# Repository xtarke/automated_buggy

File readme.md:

# Buggy AWD

Baseado em [Projeto PI3](https://github.com/luscasos/PI3-carro) de __Lucas Odair Silva.__

## Informações gerais

Projeto da placa eletrônica de potência para o acionamento de um Buggy 4x4. Um conector de 26-vias faz a conexão das seguintes placas:

- [Arduino Uno](./arduino/shield/)
- [MSP-EXP430G2](./msp430/shield_exp430g2)
- [MSP-EXP430FR2355](./msp430/shield_exp430fr2355)
- [Raspberry Pi](./rasp/)

## Características

- Controle independente dos motores (lado esquerdo e lado direito)
- Sensores de velocidade [Encoder](https://www.filipeflop.com/produto/sensor-de-velocidade-encoder/)
- Monitoramento de bateria de LiPo
- Sensor de linha dual
- Sensor ultrassom
- Comunicação Bluetooth (UART)

# Hardware

## Acionamento dos motores

Circuito final de alimentação dos motores, com queda de 0,4V de tensão na carga em relação a VCC e corrente de polarização externa de 640pA, não exigindo muita corrente do microcontrolador.

## Comunicação

## Aferição de velocidade

## Baterias
Para alimentar o carro foram escolhidas duas baterias de LIPO, de 3,7V e 1200mAh, conectadas em série, o que resulta em 7,4V de tensão.

## Regulador de tensão
Como o conjunto de baterias tem como tensão 7,4V na saída, é necessário baixar a tensão para níveis aceitáveis para o microcontrolador e modulo bluetooth, no caso foi usado um regulador ajustável Step-up-down, por questão de disponibilidade, mesmo esse sendo superdimensionado para a aplicação em questão, já que suporta correntes de até 5A e nesse caso não passa de 200mA.

## Medição da tensão das baterias
Como regra geral, não se pode descarregar uma bateria abaixo de uma certa tensão, com as usadas nesse projeto não é diferente, não sendo recomendado baixar a tensão da marca dos 3V, como o sistema possui duas baterias é necessário medir a tensão delas individualmente. O conversor analógico digital do microcontrolador tem como tensão base 3V, então é preciso baixar as tensões para menos de 3V, o circuito usado para isso é o diferencial com ampop, que pode dar um ganho menor que 1, sem usar tensão negativa. O Ampop escolhido foi o LM324, com ganho de 1/3 para a tensão superior (bateria 1 em serie com a bateria 2), e de 2/3 para a tensão media (bateria 1).

## Placa de circuito

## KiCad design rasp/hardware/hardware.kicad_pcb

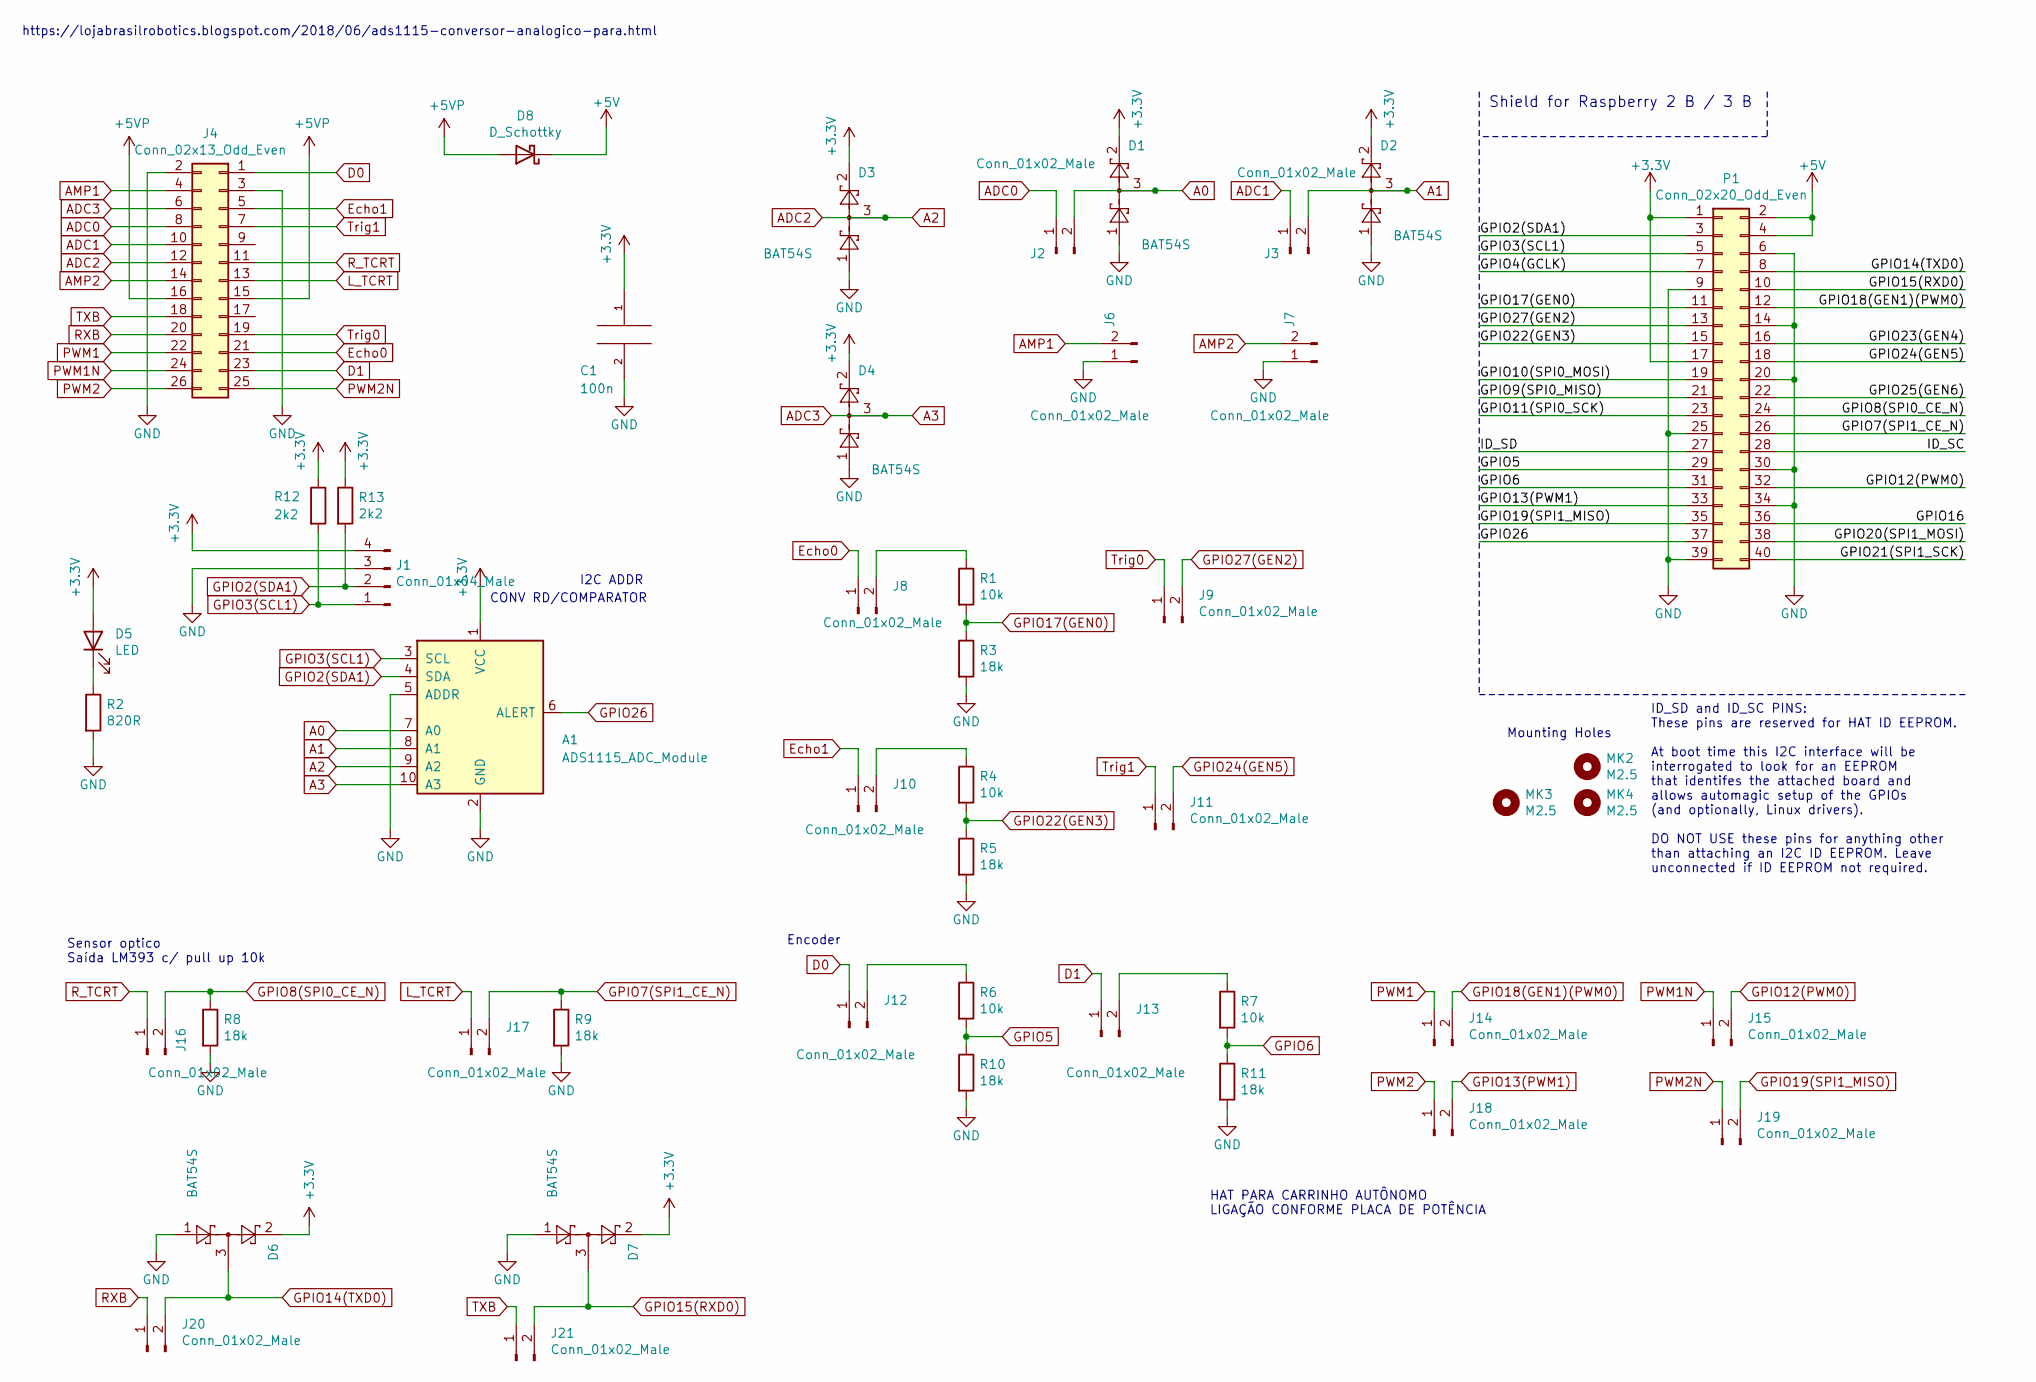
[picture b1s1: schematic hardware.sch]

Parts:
A1: ADS1115_ADC_Module; ADC1115_ADC_Module
C1: 100n; C_0805_2012Metric_Pad1.15x1.40mm_HandSolder
D1, D2, D3, D4, D6, D7: BAT54S; SOT-23
D5: LED; LED_0805_2012Metric
D8: D_Schottky; D_SMB
J1: Conn_01x04_Male; PinHeader_1x04_P2.54mm_Horizontal
J2, J3, J6, J7, J8, J9, J10, J11, J12, J13, J14, J15, J16, J17, J18, J19, J20, J21: Conn_01x02_Male; PinHeader_1x02_P2.54mm_Vertical
J4: Conn_02x13_Odd_Even; IDC-Header_2x13_P2.54mm_Vertical
MK2, MK3, MK4: M2.5; MountingHole_2.7mm_M2.5
P1: Conn_02x20_Odd_Even; PinSocket_2x20_P2.54mm_Vertical
R1, R4, R6, R7: 10k; R_0805_2012Metric
R2: 820R; R_0805_2012Metric
R3, R5, R8, R9, R10, R11: 18k; R_0805_2012Metric
R12, R13: 2k2; R_0805_2012Metric

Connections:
+3V3: A1.1 (VCC), C1.1, D1.2, D2.2, D3.2, D4.2, D5.2 (A), D6.2, D7.2, J1.4, P1.1, P1.17, R12.1, R13.1
+5V: D8.1 (K), P1.2, P1.4
+5VP: D8.2 (A), J4.15, J4.16
/GPIO4(GCLK): P1.7
/GPIO9(SPI0_MISO): P1.21
/GPIO10(SPI0_MOSI): P1.19
/GPIO11(SPI0_SCK): P1.23
/GPIO16: P1.36
/GPIO20(SPI1_MOSI): P1.38
/GPIO21(SPI1_SCK): P1.40
/GPIO23(GEN4): P1.16
/GPIO25(GEN6): P1.22
/ID_SC: P1.28
/ID_SD: P1.27
A0: A1.7 (A0), D1.3, J2.2
A1: A1.8 (A1), D2.3, J3.2
A2: A1.9 (A2), D3.3, J4.12
A3: A1.10 (A3), D4.3, J4.6
ADC0: J2.1, J4.8
ADC1: J3.1, J4.10
AMP1: J4.4, J6.2
AMP2: J4.14, J7.2
D0: J4.1, J12.1
D1: J4.23, J13.1
Echo0: J4.21, J8.1
Echo1: J4.5, J10.1
GND: A1.2 (GND), A1.5 (ADDR), C1.2, D1.1, D2.1, D3.1, D4.1, D6.1, D7.1, J1.3, J4.2, J4.3, J6.1, J7.1, P1.6, P1.9, P1.14, P1.20, P1.25, P1.30, P1.34, P1.39, R2.2, R3.2, R5.2, R8.2, R9.2, R10.2, R11.2
GPIO2(SDA1): A1.4 (SDA), J1.2, P1.3, R13.2
GPIO3(SCL1): A1.3 (SCL), J1.1, P1.5, R12.2
GPIO5: P1.29, R6.2, R10.1
GPIO6: P1.31, R7.2, R11.1
GPIO7(SPI1_CE_N): J17.2, P1.26, R9.1
GPIO8(SPI0_CE_N): J16.2, P1.24, R8.1
GPIO12(PWM0): J15.2, P1.32
GPIO13(PWM1): J18.2, P1.33
GPIO14(TXD0): D6.3, J20.2, P1.8
GPIO15(RXD0): D7.3, J21.2, P1.10
GPIO17(GEN0): P1.11, R1.2, R3.1
GPIO18(GEN1)(PWM0): J14.2, P1.12
GPIO19(SPI1_MISO): J19.2, P1.35
GPIO22(GEN3): P1.15, R4.2, R5.1
GPIO24(GEN5): J11.2, P1.18
GPIO26: A1.6 (ALERT), P1.37
GPIO27(GEN2): J9.2, P1.13
L_TCRT: J4.13, J17.1
unnamed: D5.1 (K), R2.1
unnamed: J8.2, R1.1
unnamed: J10.2, R4.1
unnamed: J12.2, R6.1
unnamed: J13.2, R7.1
PWM1: J4.22, J14.1
PWM1N: J4.24, J15.1
PWM2: J4.26, J18.1
PWM2N: J4.25, J19.1
RXB: J4.20, J20.1
R_TCRT: J4.11, J16.1
TXB: J4.18, J21.1
Trig0: J4.19, J9.1
Trig1: J4.7, J11.1

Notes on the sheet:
ID_SD and ID_SC PINS: These pins are reserved for HAT ID EEPROM. At boot time this I2C interface will be interrogated to look for an EEPROM that identifes the attached board and allows automagic setup of the GPIOs (and optionally, Linux drivers). DO NOT USE these pins for anything other than attach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
Mounting Holes
Shield for Raspberry 2 B / 3 B
Encoder
Sensor optico Saída LM393 c/ pull up 10k
HAT PARA CARRINHO AUTÔNOMO LIGAÇÃO CONFORME PLACA DE POTÊNCIA
https://lojabrasilrobotics.blogspot.com/2018/06/ads1115-conversor-analogico-para.html
I2C ADDR
CONV RD/COMPARATOR

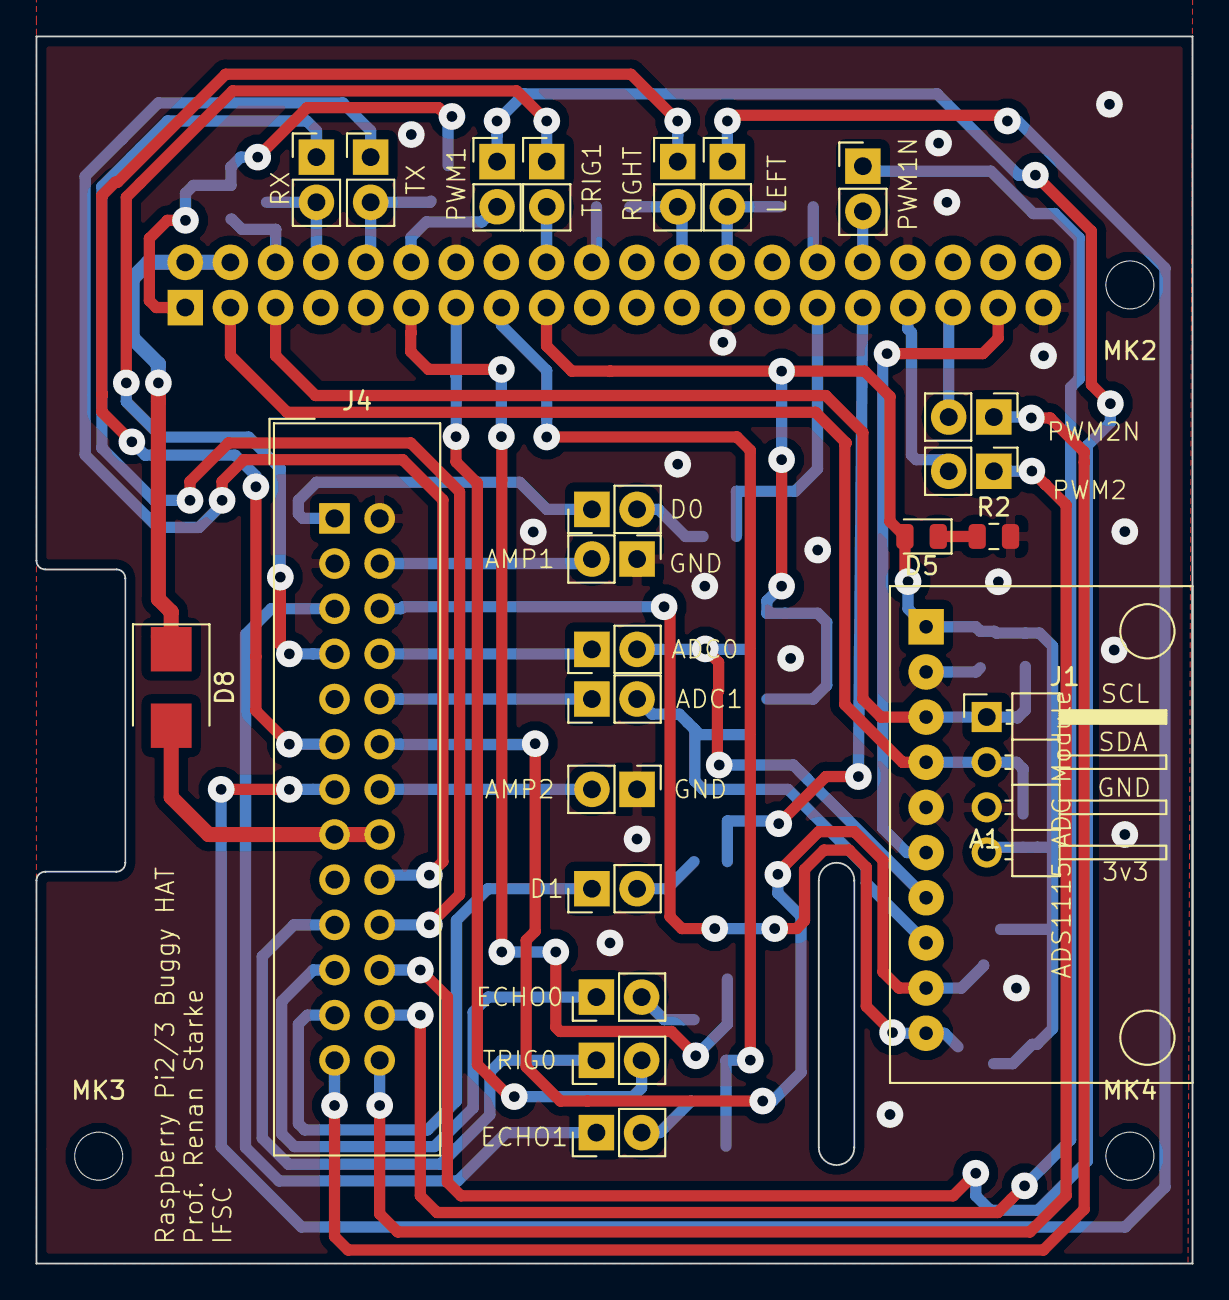
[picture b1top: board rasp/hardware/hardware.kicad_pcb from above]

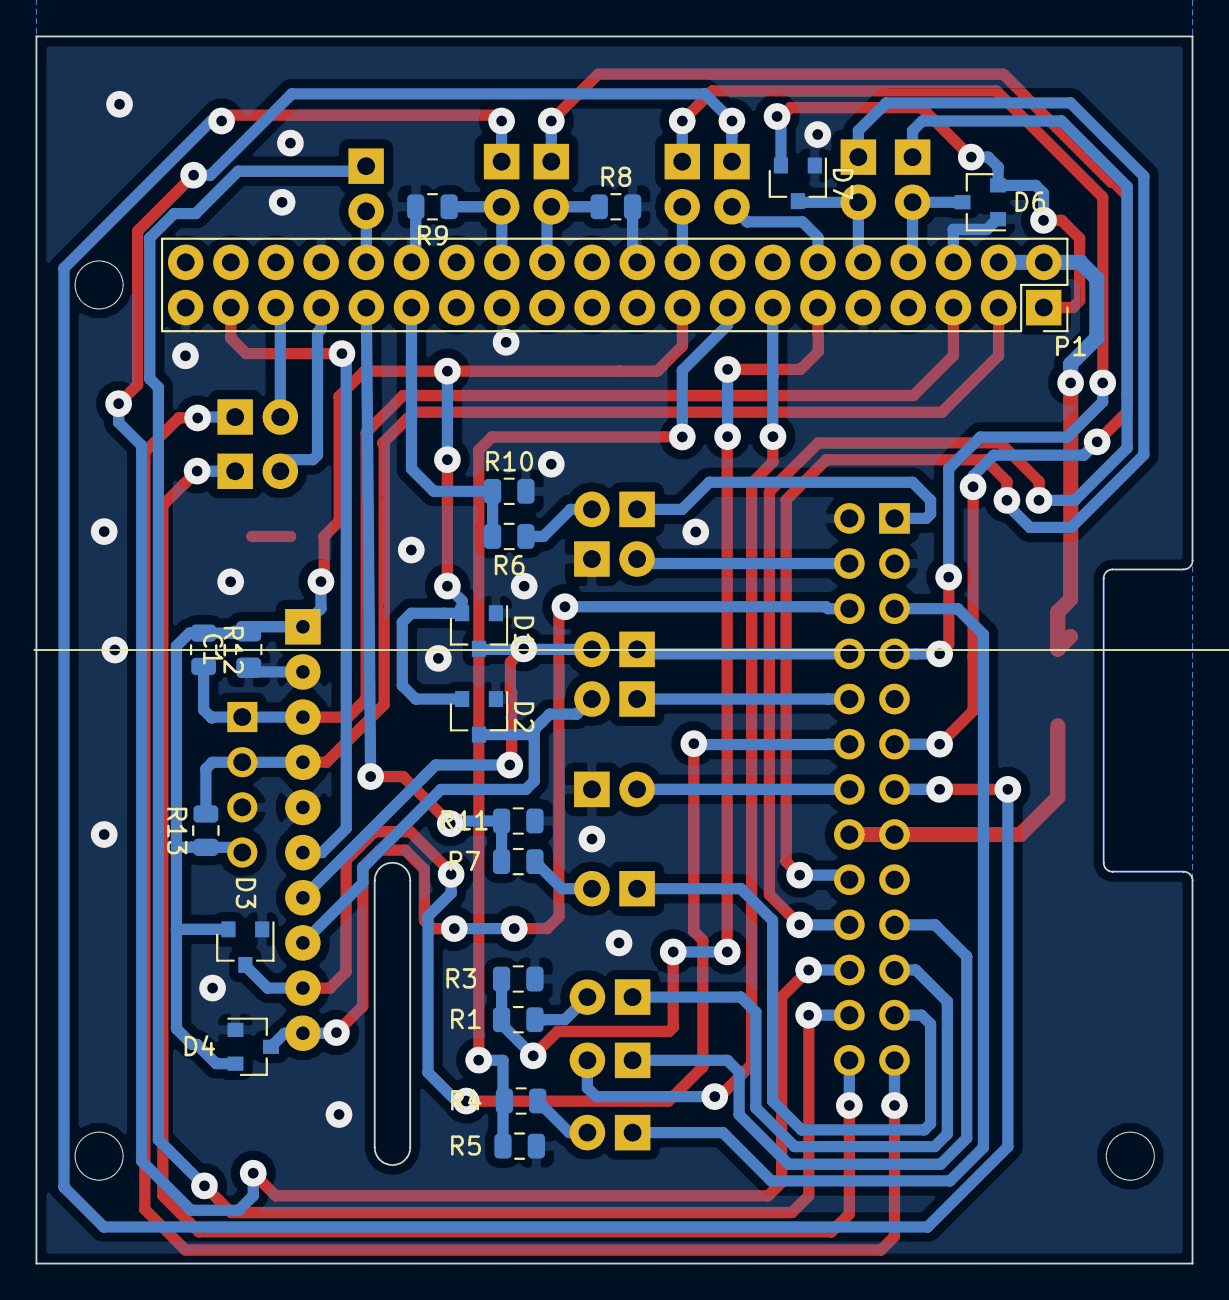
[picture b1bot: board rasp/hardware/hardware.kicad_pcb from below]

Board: 2 copper layers, 65.0 x 69.0 mm, 47 parts (20 on the bottom side), 48 nets.

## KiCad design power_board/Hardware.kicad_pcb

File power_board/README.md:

# Placa de potência para Buggy AWD

Baseado em [Projeto PI3](https://github.com/luscasos/PI3-carro) de __Lucas Odair Silva.__

## Informações gerais

Projeto da placa eletrônica de potência para o acionamento de um Buggy 4x4. Um conector de 26-vias faz a conexão das seguintes placas:

- [Arduino Uno](https://github.com/xtarke/avrlibs/tree/master/shields/carrinho_shield)
- [MSP-EXP430G2](https://github.com/xtarke/msplibs/tree/master/hardware/shield_exp430g2)
- [MSP-EXP430FR2355](https://github.com/xtarke/msplibs/tree/master/hardware/shield_exp430fr2355)
- [Raspberry Pi](https://github.com/xtarke/automated_buggy)

## Características

- Controle independente dos motores (lado esquerdo e lado direito)
- Sensores de velocidade [Encoder](https://www.filipeflop.com/produto/sensor-de-velocidade-encoder/)
- Monitoramento de bateria de LiPo
- Sensor de linha dual
- Sensor ultrassom
- Comunicação Bluetooth (UART)

# Hardware

## Acionamento dos motores

Circuito final de alimentação dos motores, com queda de 0,4V de tensão na carga em relação a VCC e corrente de polarização externa de 640pA, não exigindo muita corrente do microcontrolador.

## Comunicação

## Aferição de velocidade

## Baterias
Para alimentar o carro foram escolhidas duas baterias de LIPO, de 3,7V e 1200mAh, conectadas em série, o que resulta em 7,4V de tensão.

## Regulador de tensão
Como o conjunto de baterias tem como tensão 7,4V na saída, é necessário baixar a tensão para níveis aceitáveis para o microcontrolador e modulo bluetooth, no caso foi usado um regulador ajustável Step-up-down, por questão de disponibilidade, mesmo esse sendo superdimensionado para a aplicação em questão, já que suporta correntes de até 5A e nesse caso não passa de 200mA.

## Medição da tensão das baterias
Como regra geral, não se pode descarregar uma bateria abaixo de uma certa tensão, com as usadas nesse projeto não é diferente, não sendo recomendado baixar a tensão da marca dos 3V, como o sistema possui duas baterias é necessário medir a tensão delas individualmente. O conversor analógico digital do microcontrolador tem como tensão base 3V, então é preciso baixar as tensões para menos de 3V, o circuito usado para isso é o diferencial com ampop, que pode dar um ganho menor que 1, sem usar tensão negativa. O Ampop escolhido foi o LM324, com ganho de 1/3 para a tensão superior (bateria 1 em serie com a bateria 2), e de 2/3 para a tensão media (bateria 1).

## Placa de circuito

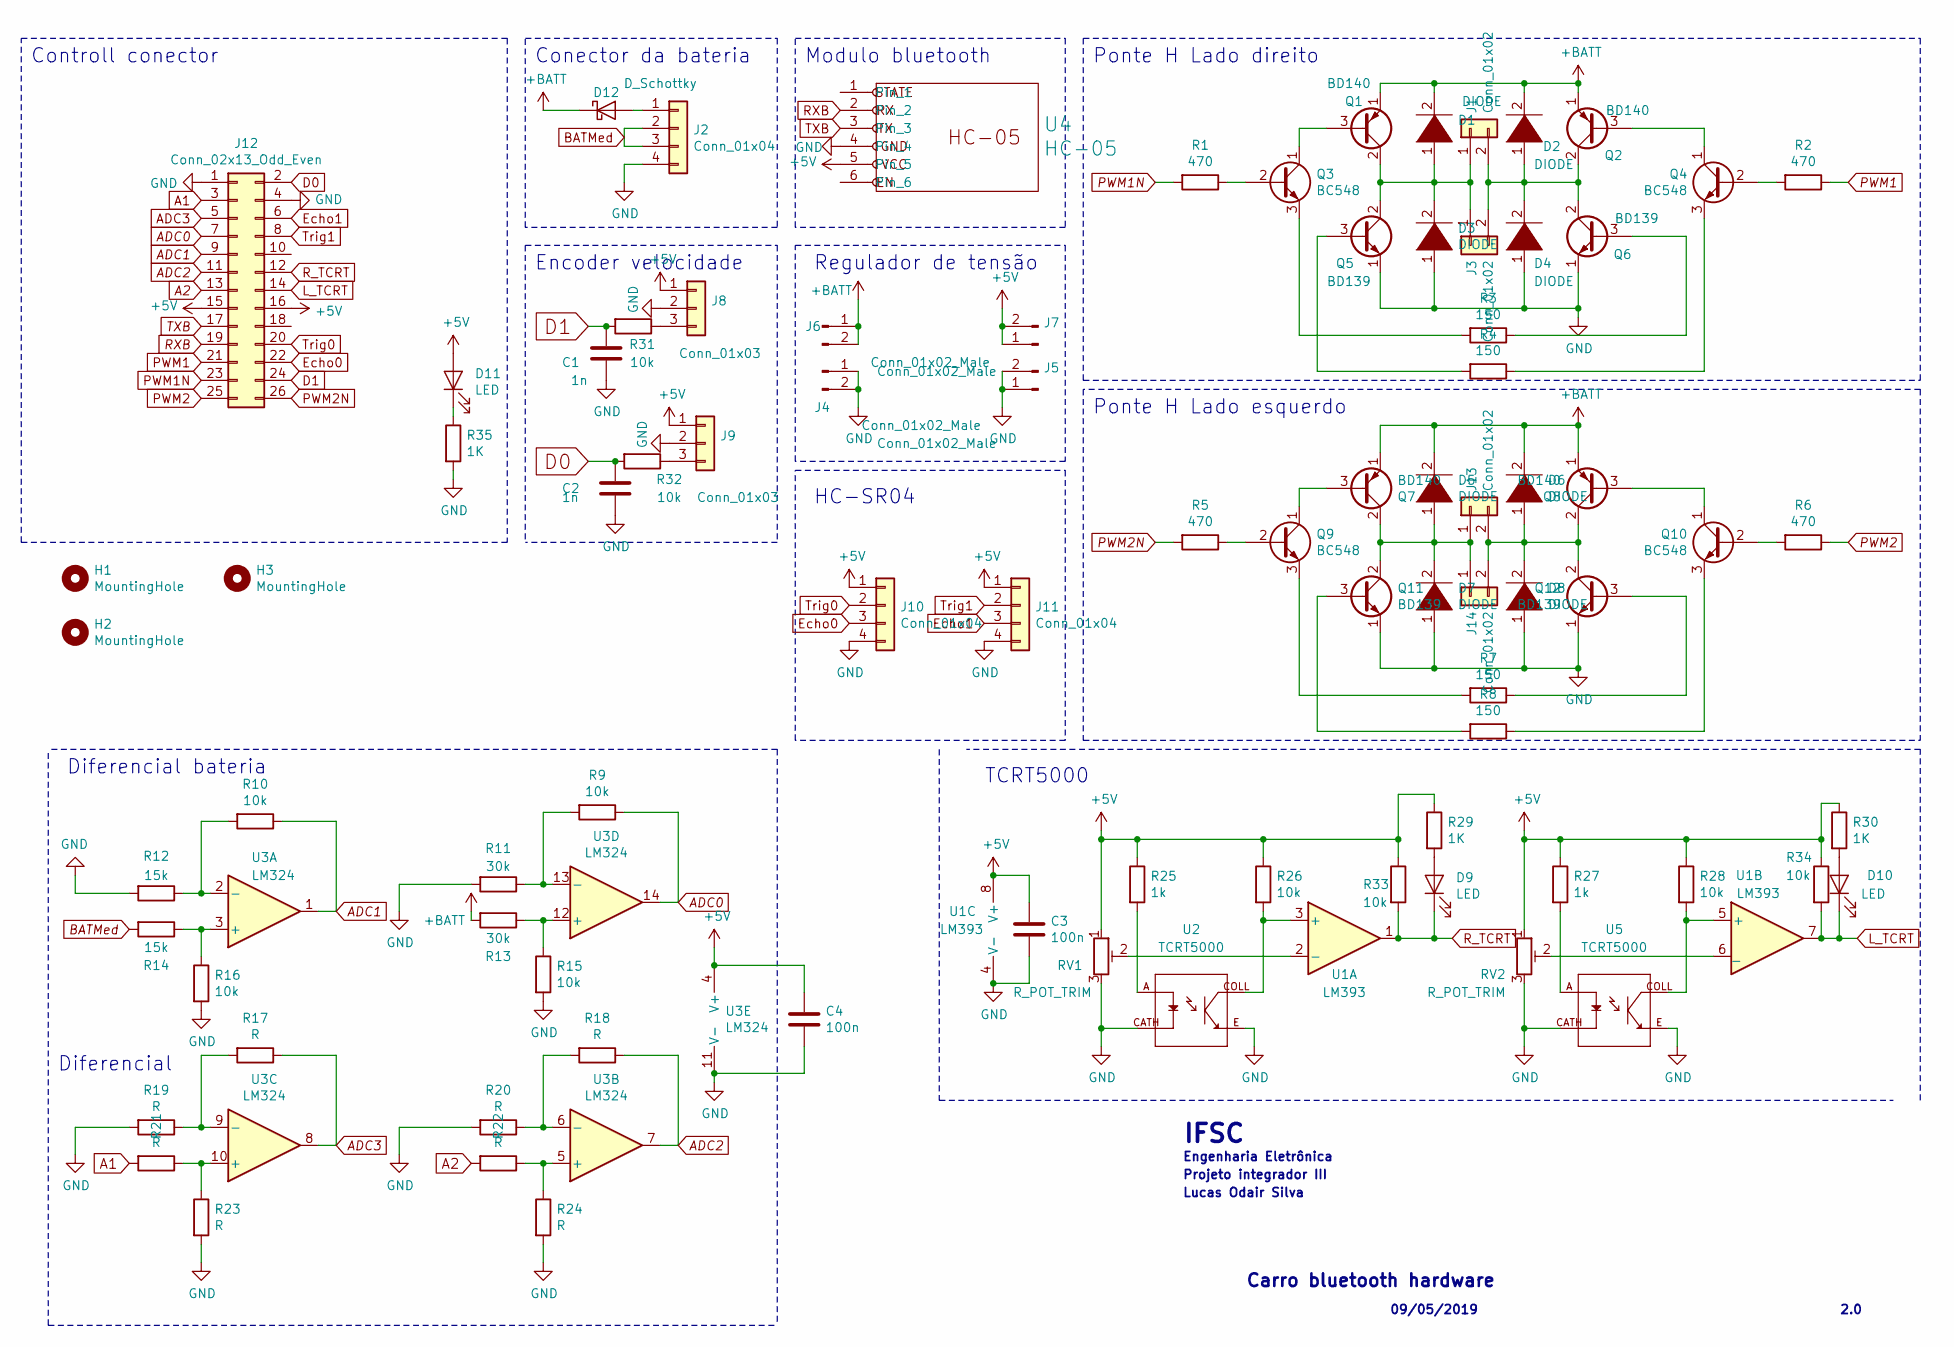
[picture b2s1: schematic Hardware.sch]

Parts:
C1, C2: 1n; C_0805_2012Metric_Pad1.15x1.40mm_HandSolder
C3, C4: 100n; C_0805_2012Metric
D1, D2, D3, D4, D5, D6, D7, D8: DIODE; D_A-405_P2.54mm_Vertical_AnodeUp
D9, D10, D11: LED; LED_0805_2012Metric
D12: D_Schottky; D_SMB
H1, H2, H3: MountingHole; MountingHole_3.2mm_M3
J1, J3, J13, J14: Conn_01x02; PinHeader_1x02_P2.54mm_Vertical
J2, J10, J11: Conn_01x04; PinHeader_1x04_P2.54mm_Vertical
J4, J5, J6, J7: Conn_01x02_Male; PinSocket_1x02_P2.54mm_Vertical
J8, J9: Conn_01x03; PinHeader_1x03_P2.54mm_Vertical
J12: Conn_02x13_Odd_Even; PinSocket_2x13_P2.54mm_Vertical
Q1, Q2, Q7, Q8: BD140; TO-126-3_Vertical
Q3, Q4, Q9, Q10: BC548; TO-92_Inline_Wide
Q5, Q6, Q11, Q12: BD139; TO-126-3_Vertical
R1, R2, R5, R6: 470; R_0805_2012Metric
R3, R4, R7, R8: 150; R_0805_2012Metric
R9, R10, R15, R16, R26, R28: 10k; R_0805_2012Metric
R11, R13: 30k; R_0805_2012Metric
R12, R14: 15k; R_0805_2012Metric
R17, R18, R19, R20, R21, R22, R23, R24: R; R_0805_2012Metric
R25, R27: 1k; R_0805_2012Metric
R29, R30, R35: 1K; R_0805_2012Metric
R31, R32, R33, R34: 10k; R_0805_2012Metric_Pad1.15x1.40mm_HandSolder
RV1, RV2: R_POT_TRIM; Potentiometer_Piher_PT-6-V_Vertical
U1: LM393
U2, U5: TCRT5000; OPTO_TCRT5000
U3: LM324
U4: HC-05; PinHeader_1x06_P2.54mm_Horizontal

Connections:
+5V: C3.1, C4.1, D11.2 (A), J7.1, J7.2, J8.1, J9.1, J10.1, J11.1, J12.15, J12.16, R25.1, R26.1, R27.1, R28.1, R29.1, R30.1, R33.1, R34.1, RV1.1, RV2.1, U1.8 (V+), U3.4 (V+), U4.5
+BATT: D1.2 (A), D2.2 (A), D5.2 (A), D6.2 (A), D12.1 (K), J6.1, J6.2, Q1.1 (E), Q2.1 (E), Q7.1 (E), Q8.1 (E), R13.2
A1: J12.3, R21.2
A2: J12.13, R22.2
ADC0: J12.7, R9.1, U3.14
ADC1: J12.9, R10.1, U3.1
ADC2: J12.11, R18.1, U3.7
ADC3: J12.5, R17.1, U3.8
BATMed: J2.2, J2.3, R14.2
D0: C2.1, J12.2, R32.2
D1: C1.1, J12.24, R31.2
Echo0: J10.3, J12.22
Echo1: J11.3, J12.6
GND: C1.2, C2.2, C3.2, C4.2, D3.1 (K), D4.1 (K), D7.1 (K), D8.1 (K), J2.4, J4.1, J4.2, J5.1, J5.2, J8.2, J9.2, J10.4, J11.4, J12.1, J12.4, Q5.1 (E), Q6.1 (E), Q11.1 (E), Q12.1 (E), R11.2, R12.2, R15.2, R16.2, R19.2, R20.2, R23.2, R24.2, R35.2, RV1.3, RV2.3, U1.4 (V-), U2.CATH, U2.E, U3.11 (V-), U4.4, U5.CATH, U5.E
L_TCRT: D10.1 (K), J12.14, R34.2, U1.7
unnamed: D1.1 (K), D3.2 (A), J1.1, J3.1, Q1.2 (C), Q5.2 (C)
unnamed: D2.1 (K), D4.2 (A), J1.2, J3.2, Q2.2 (C), Q6.2 (C)
unnamed: D5.1 (K), D7.2 (A), J13.1, J14.1, Q7.2 (C), Q11.2 (C)
unnamed: D6.1 (K), D8.2 (A), J13.2, J14.2, Q8.2 (C), Q12.2 (C)
unnamed: D9.2 (A), R29.2
unnamed: D10.2 (A), R30.2
unnamed: D11.1 (K), R35.1
unnamed: D12.2 (A), J2.1
unnamed: J8.3, R31.1
unnamed: J9.3, R32.1
unnamed: Q1.3 (B), Q3.1 (C)
unnamed: Q2.3 (B), Q4.1 (C)
unnamed: Q3.2 (B), R1.1
unnamed: Q3.3 (E), R3.2
unnamed: Q4.2 (B), R2.2
unnamed: Q4.3 (E), R4.1
unnamed: Q5.3 (B), R4.2
unnamed: Q6.3 (B), R3.1
unnamed: Q7.3 (B), Q9.1 (C)
unnamed: Q9.2 (B), R5.1
unnamed: Q9.3 (E), R7.2
unnamed: Q8.3 (B), Q10.1 (C)
unnamed: Q10.2 (B), R6.2
unnamed: Q10.3 (E), R8.1
unnamed: Q11.3 (B), R8.2
unnamed: Q12.3 (B), R7.1
unnamed: R10.2, R12.1, U3.2 (-)
unnamed: R9.2, R11.1, U3.13 (-)
unnamed: R13.1, R15.1, U3.12 (+)
unnamed: R14.1, R16.1, U3.3 (+)
unnamed: R17.2, R19.1, U3.9 (-)
unnamed: R18.2, R20.1, U3.6 (-)
unnamed: R21.1, R23.1, U3.10 (+)
unnamed: R22.1, R24.1, U3.5 (+)
unnamed: R25.2, U2.A
unnamed: R26.2, U1.3 (+), U2.COLL
unnamed: R27.2, U5.A
unnamed: R28.2, U1.5 (+), U5.COLL
unnamed: RV1.2, U1.2 (-)
unnamed: RV2.2, U1.6 (_)
PWM1: J12.21, R2.1
PWM1N: J12.23, R1.2
PWM2: J12.25, R6.1
PWM2N: J12.26, R5.2
RXB: J12.19, U4.2
R_TCRT: D9.1 (K), J12.12, R33.2, U1.1
TXB: J12.17, U4.3
Trig0: J10.2, J12.20
Trig1: J11.2, J12.8

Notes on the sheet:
Carro bluetooth hardware
09/05/2019
2.0
IFSC
Projeto integrador III
Lucas Odair Silva
Engenharia Eletrônica
Ponte H Lado direito
Ponte H Lado esquerdo
Diferencial bateria
Modulo bluetooth
Conector da bateria
Regulador de tensão
Controll conector
Encoder velocidade
Diferencial
HC-SR04
TCRT5000

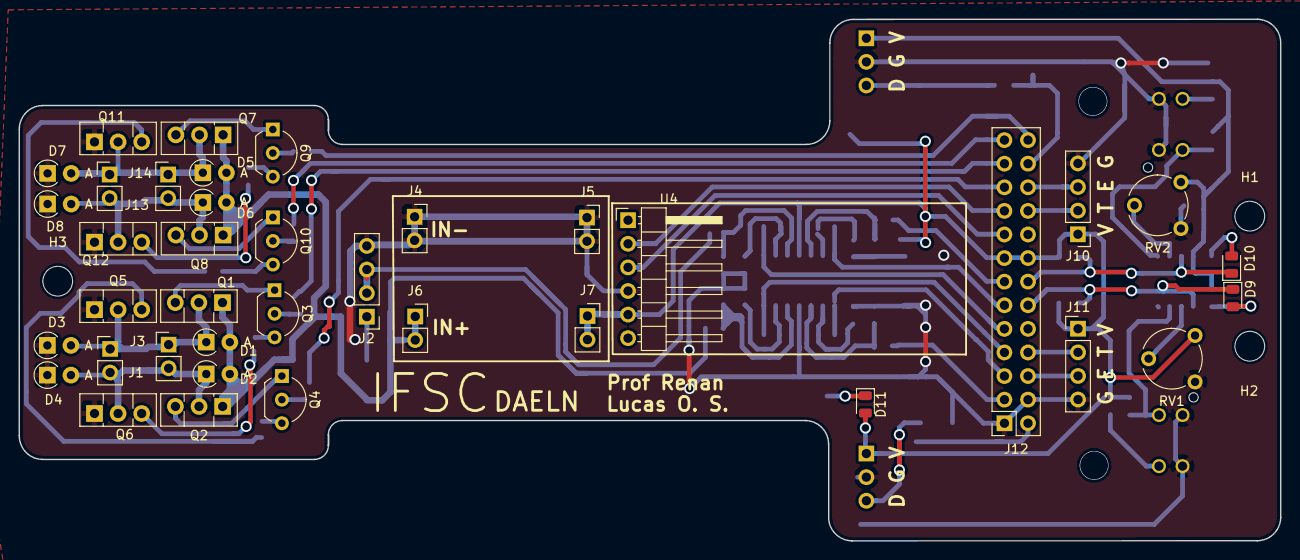
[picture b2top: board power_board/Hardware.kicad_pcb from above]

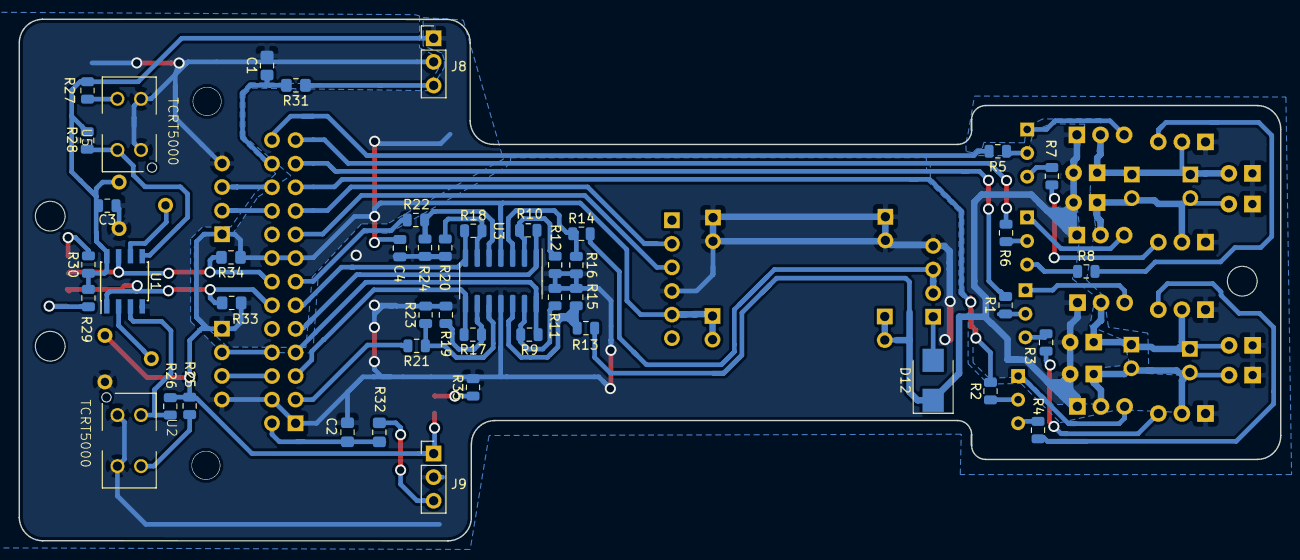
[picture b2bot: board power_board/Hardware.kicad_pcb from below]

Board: 2 copper layers, 135.7 x 56.1 mm, 87 parts (46 on the bottom side), 64 nets.

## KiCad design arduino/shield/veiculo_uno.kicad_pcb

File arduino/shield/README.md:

# Interface shield

This shield connects Arduino Uno pins to the car's power board. Go to [Power Board](https://github.com/xtarke/avrlibs/tree/master/shields/carrinho_potencia) for more hardware information.

See [this schematic](schematic.pdf).

## Analog pins

| Analog input  | Arduino pin  | Board label  | Signal |
| ------------- | -------- | ------------ | ------ |
| ADC0          | A2       |   ADC0       | Bat0   |
| ADC1          | A1       |   ADC1       | Bat1   |
| ADC2          | A0       |   ADC2       | Ampop1 |
| ADC3          | A3       |   ADC3       | Ampop2 |

## Ultrasonic sensor

| Arduino Pin | Signal|
| ------- | ------|
| 8       | Echo0 |
| 7       | Trig0 |
| 2       | Echo1 |
| 4       | Trig1 |

## Motors

|Arduino Pin | Signal|  Board label |
| ---------- | ------| ------------ |
| 6          | PWM1  |  M1          |
| 5          | PWM1N |  M1N         |
| 11         | PWM2  |  M2          |
| 3          | PWM2N |  M2N         |

## Espeed econder

| Arduino Pin | Signal |  Board label |
| ----------- | ------ | ------------ |
| 13          | D0     | ENC0         |
| 12          | D1     | ENC1         |

## Optic sensor

| Arduino Pin | Signal | Board label |
| ----------- | ------ | ----------- |
| A4          | R_TCRT | R DIR       |
| A5          | L_TCRT | L ESQ       |

## UART

| MSP Pin | Signal |
| ------- | ------ |
| TX      | TX     |
| RX      | RX     |

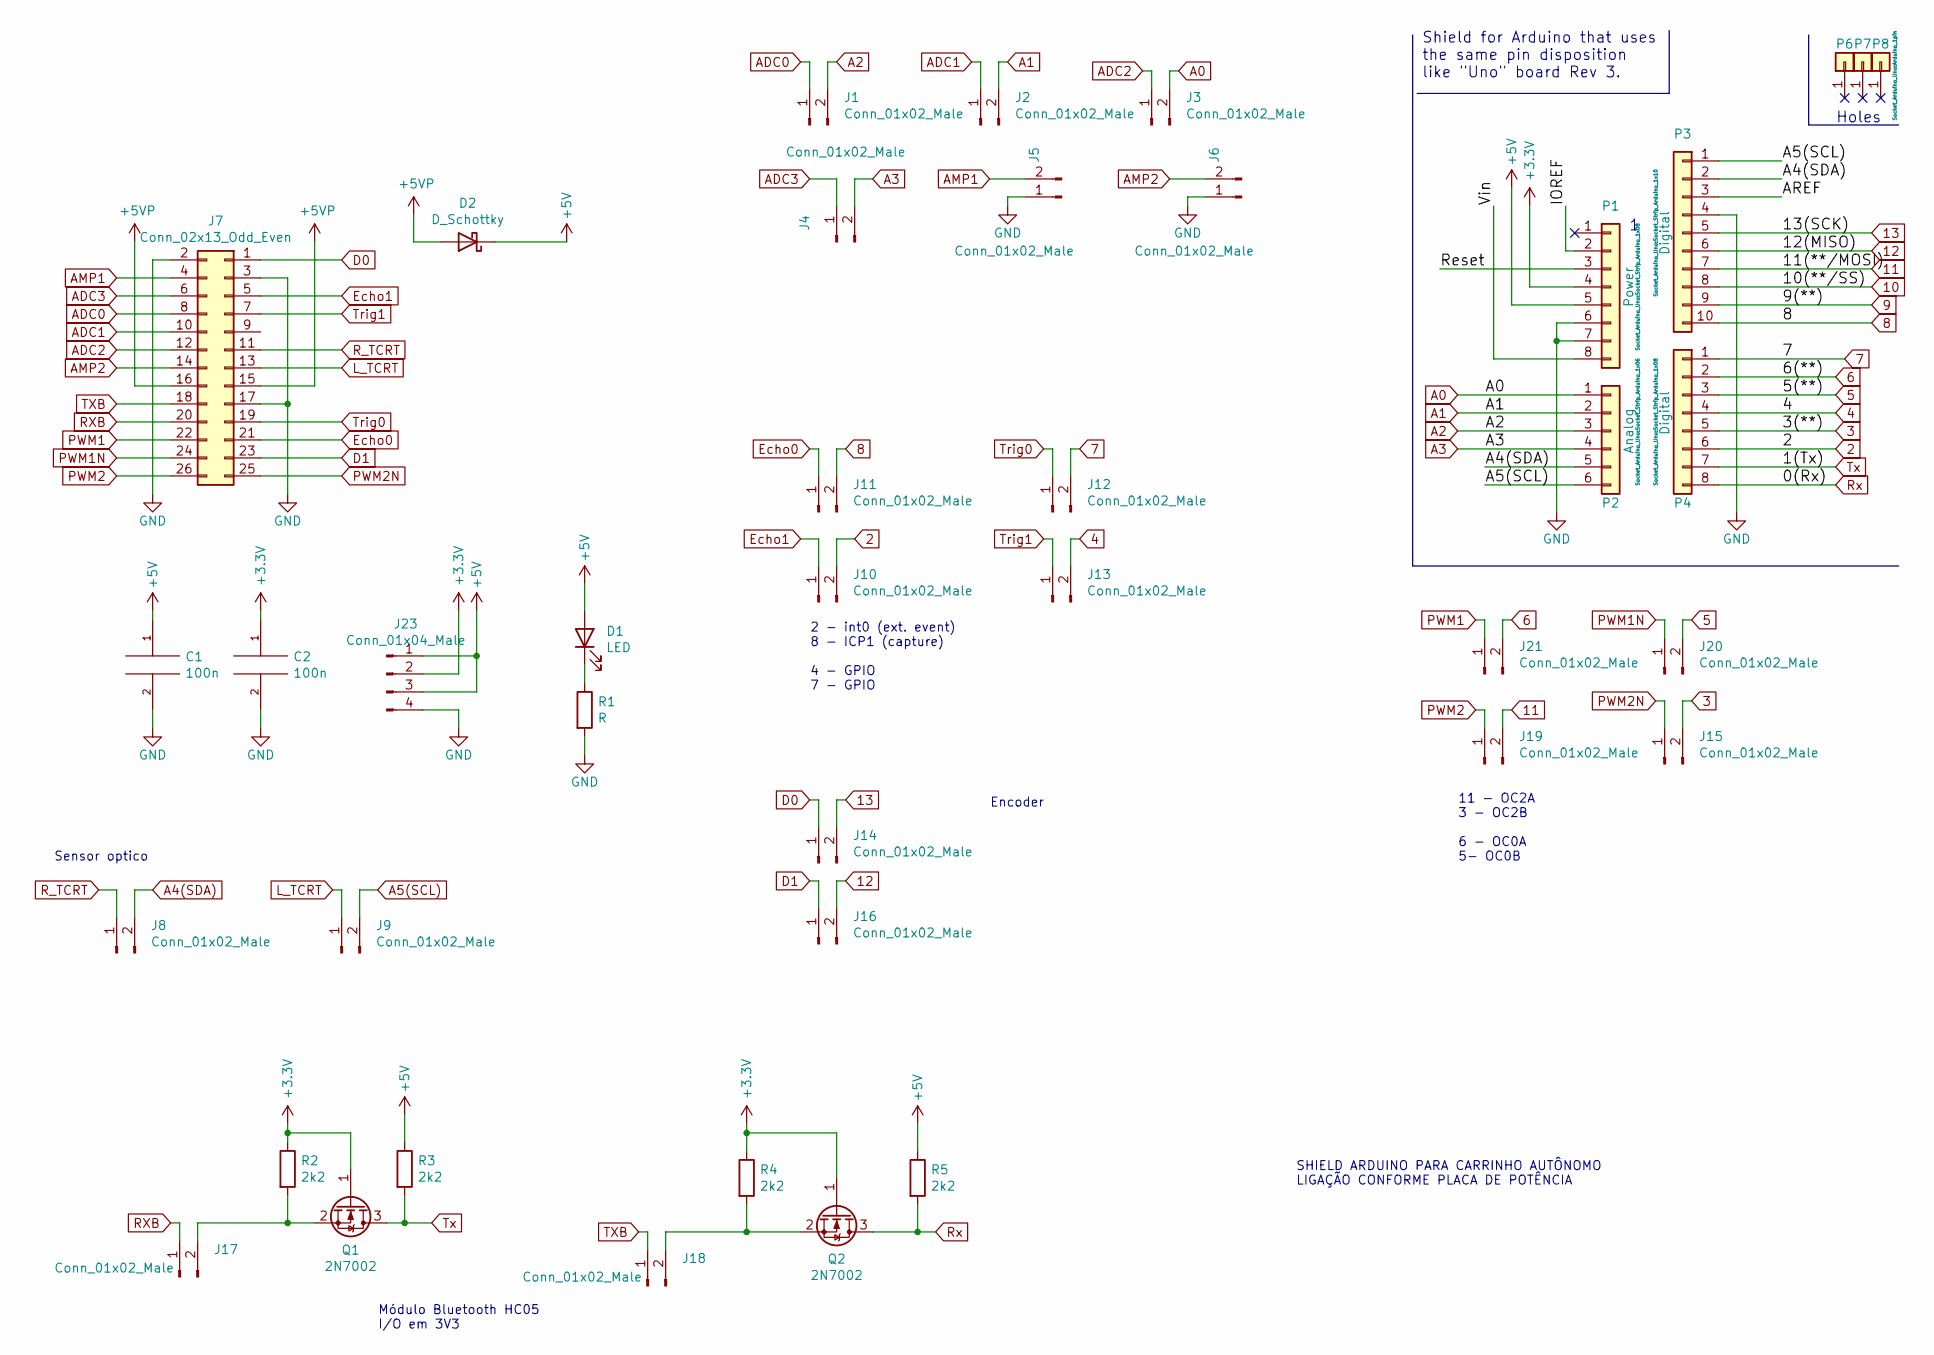
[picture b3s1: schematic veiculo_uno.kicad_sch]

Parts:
C1, C2: 100n; C_0805_2012Metric_Pad1.15x1.40mm_HandSolder
D1: LED; LED_0805_2012Metric
D2: D_Schottky; D_SMB
J1, J2, J3, J4, J5, J6, J8, J9, J10, J11, J12, J13, J14, J15, J16, J17, J18, J19, J20, J21: Conn_01x02_Male; PinHeader_1x02_P2.54mm_Vertical
J7: Conn_02x13_Odd_Even; IDC-Header_2x13_P2.54mm_Vertical
J23: Conn_01x04_Male; PinHeader_1x04_P2.54mm_Vertical
P1: Power; Socket_Strip_Arduino_1x08
P2: Analog; Socket_Strip_Arduino_1x06
P3: Digital; Socket_Strip_Arduino_1x10
P4: Digital; Socket_Strip_Arduino_1x08
P6, P7, P8: CONN_01X01; Arduino_1pin
Q1, Q2: 2N7002; SOT-23
R1: R; R_0805_2012Metric
R2, R3, R4, R5: 2k2; R_0805_2012Metric

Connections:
2: J10.2, P4.6
3: J15.2, P4.5
4: J13.2, P4.4
5: J20.2, P4.3
6: J21.2, P4.2
7: J12.2, P4.1
8: J11.2, P3.10
9: P3.9
10: P3.8
11: J19.2, P3.7
12: J16.2, P3.6
13: J14.2, P3.5
+3V3: C2.1, J23.2, P1.4, Q1.1 (G), Q2.1 (G), R2.1, R4.1
+5V: C1.1, D1.2 (A), D2.1 (K), J23.1, J23.3, P1.5, R3.1, R5.1
+5VP: D2.2 (A), J7.15, J7.16
/AREF: P3.3
/IOREF: P1.2
/Reset: P1.3
/Vin: P1.8
A0: J3.2, P2.1
A1: J2.2, P2.2
A2: J1.2, P2.3
A3: J4.2, P2.4
A4(SDA): J8.2, P2.5, P3.2
A5(SCL): J9.2, P2.6, P3.1
ADC0: J1.1, J7.8
ADC1: J2.1, J7.10
ADC2: J3.1, J7.12
ADC3: J4.1, J7.6
AMP1: J5.2, J7.4
AMP2: J6.2, J7.14
D0: J7.1, J14.1
D1: J7.23, J16.1
Echo0: J7.21, J11.1
Echo1: J7.5, J10.1
GND: C1.2, C2.2, J5.1, J6.1, J7.2, J7.3, J7.17, J23.4, P1.6, P1.7, P3.4, R1.2
L_TCRT: J7.13, J9.1
unnamed: D1.1 (K), R1.1
unnamed: J17.2, Q1.2 (S), R2.2
unnamed: J18.2, Q2.2 (S), R4.2
PWM1: J7.22, J21.1
PWM1N: J7.24, J20.1
PWM2: J7.26, J19.1
PWM2N: J7.25, J15.1
RXB: J7.20, J17.1
R_TCRT: J7.11, J8.1
Rx: P4.8, Q2.3 (D), R5.2
TXB: J7.18, J18.1
Trig0: J7.19, J12.1
Trig1: J7.7, J13.1
Tx: P4.7, Q1.3 (D), R3.2

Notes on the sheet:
11 - OC2A 3 - OC2B 6 - OC0A 5- OC0B
Módulo Bluetooth HC05 I/O em 3V3
SHIELD ARDUINO PARA CARRINHO AUTÔNOMO LIGAÇÃO CONFORME PLACA DE POTÊNCIA
2 - int0 (ext. event) 8 - ICP1 (capture) 4 - GPIO 7 - GPIO
Encoder
Shield for Arduino that uses the same pin disposition like "Uno" board Rev 3.
Sensor optico
Holes

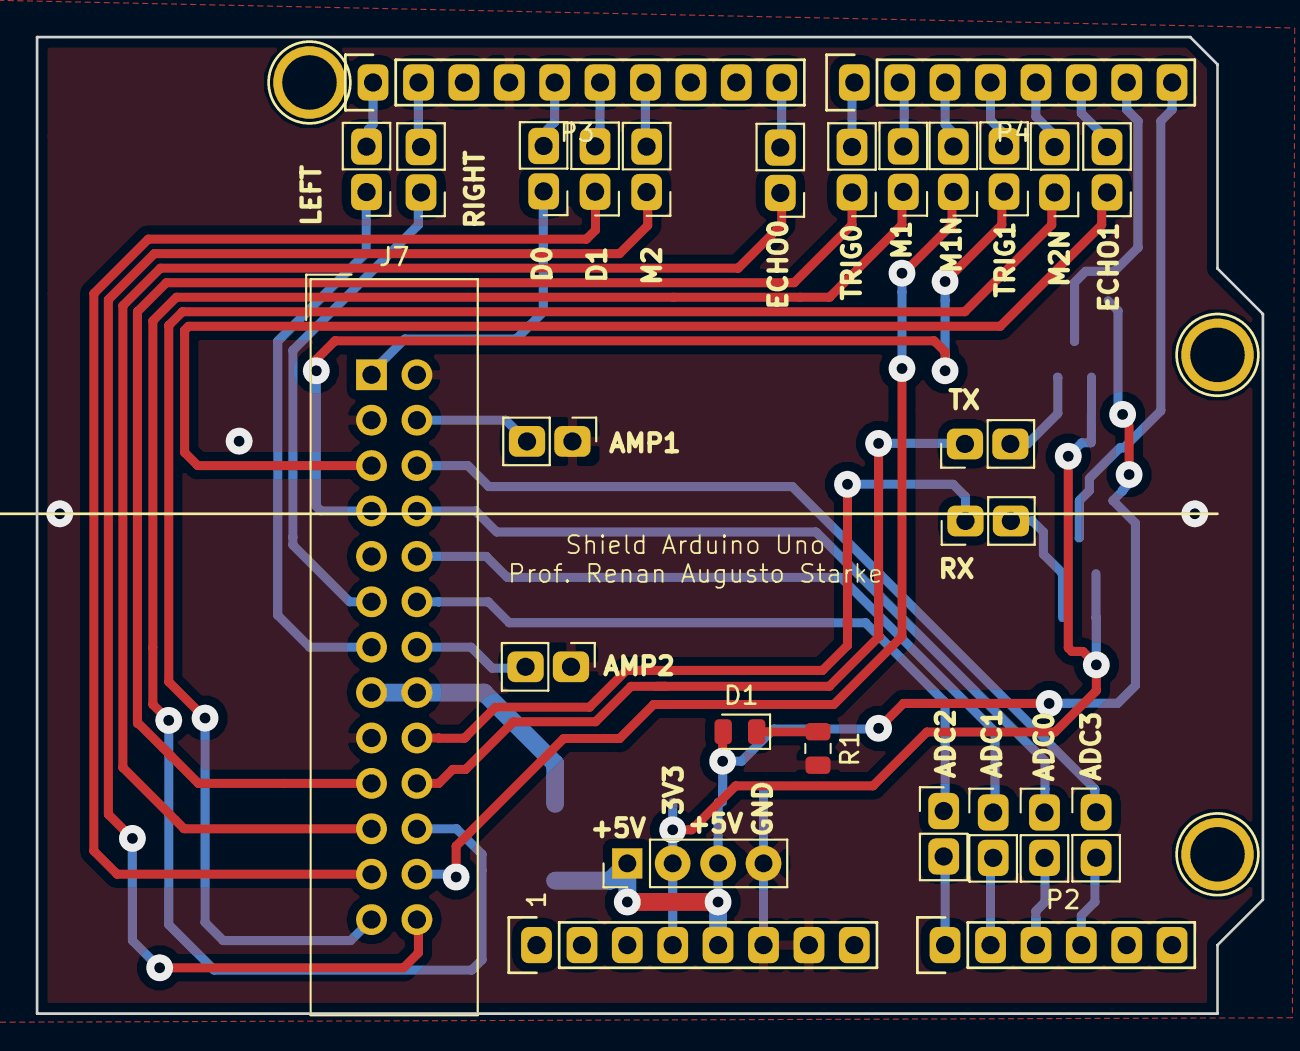
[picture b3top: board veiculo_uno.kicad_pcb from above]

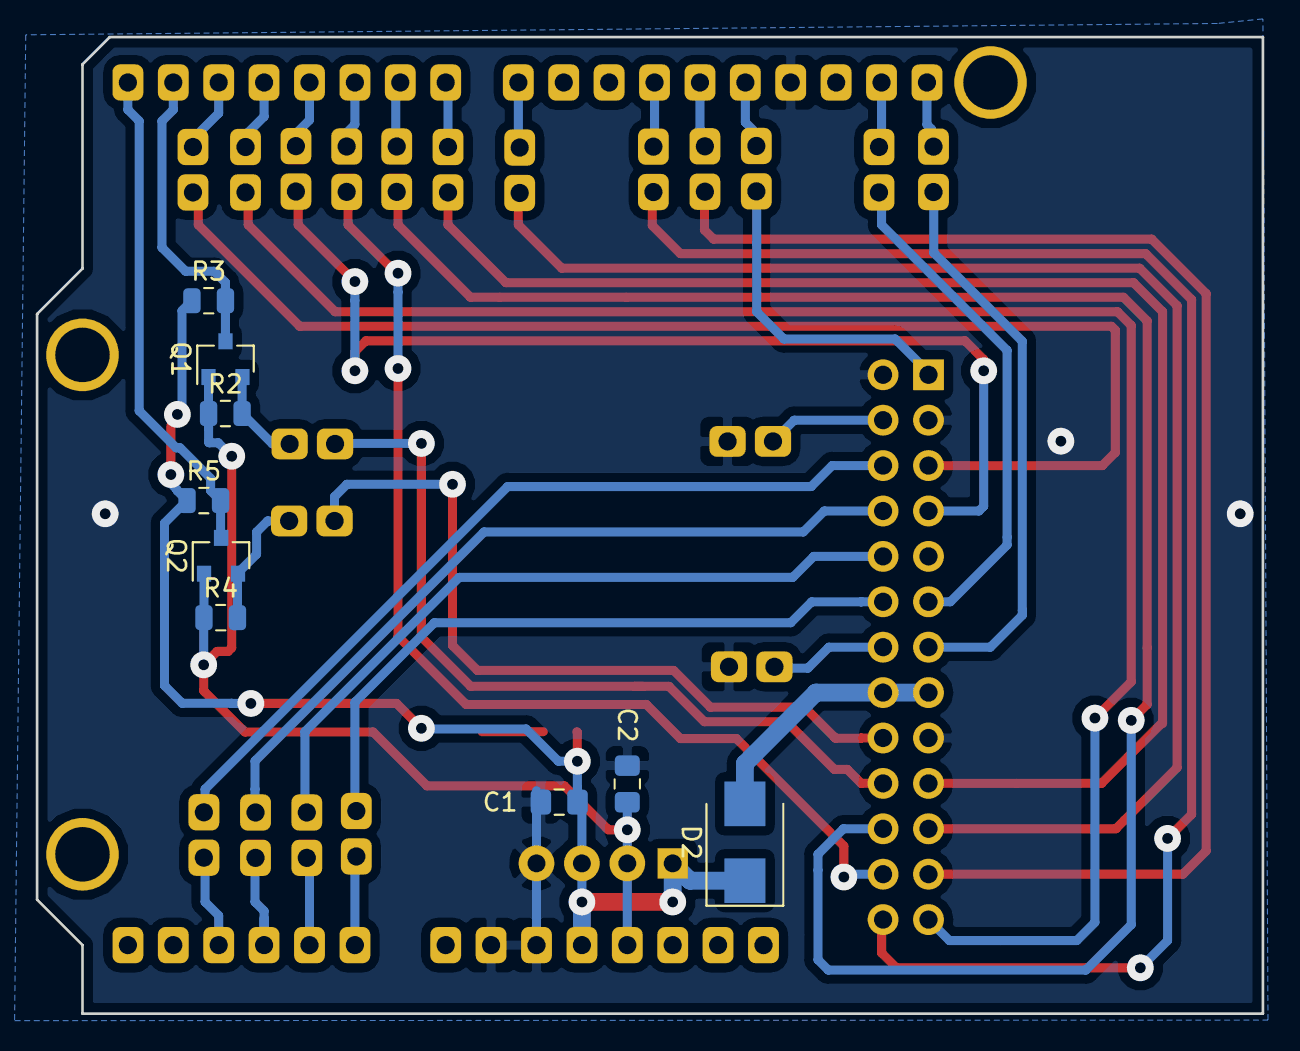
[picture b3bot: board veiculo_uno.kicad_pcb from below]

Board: 2 copper layers, 68.6 x 54.6 mm, 40 parts (9 on the bottom side), 45 nets.
